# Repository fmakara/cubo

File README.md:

# cubo
C.U.B.O. - Montador de cubo mágico

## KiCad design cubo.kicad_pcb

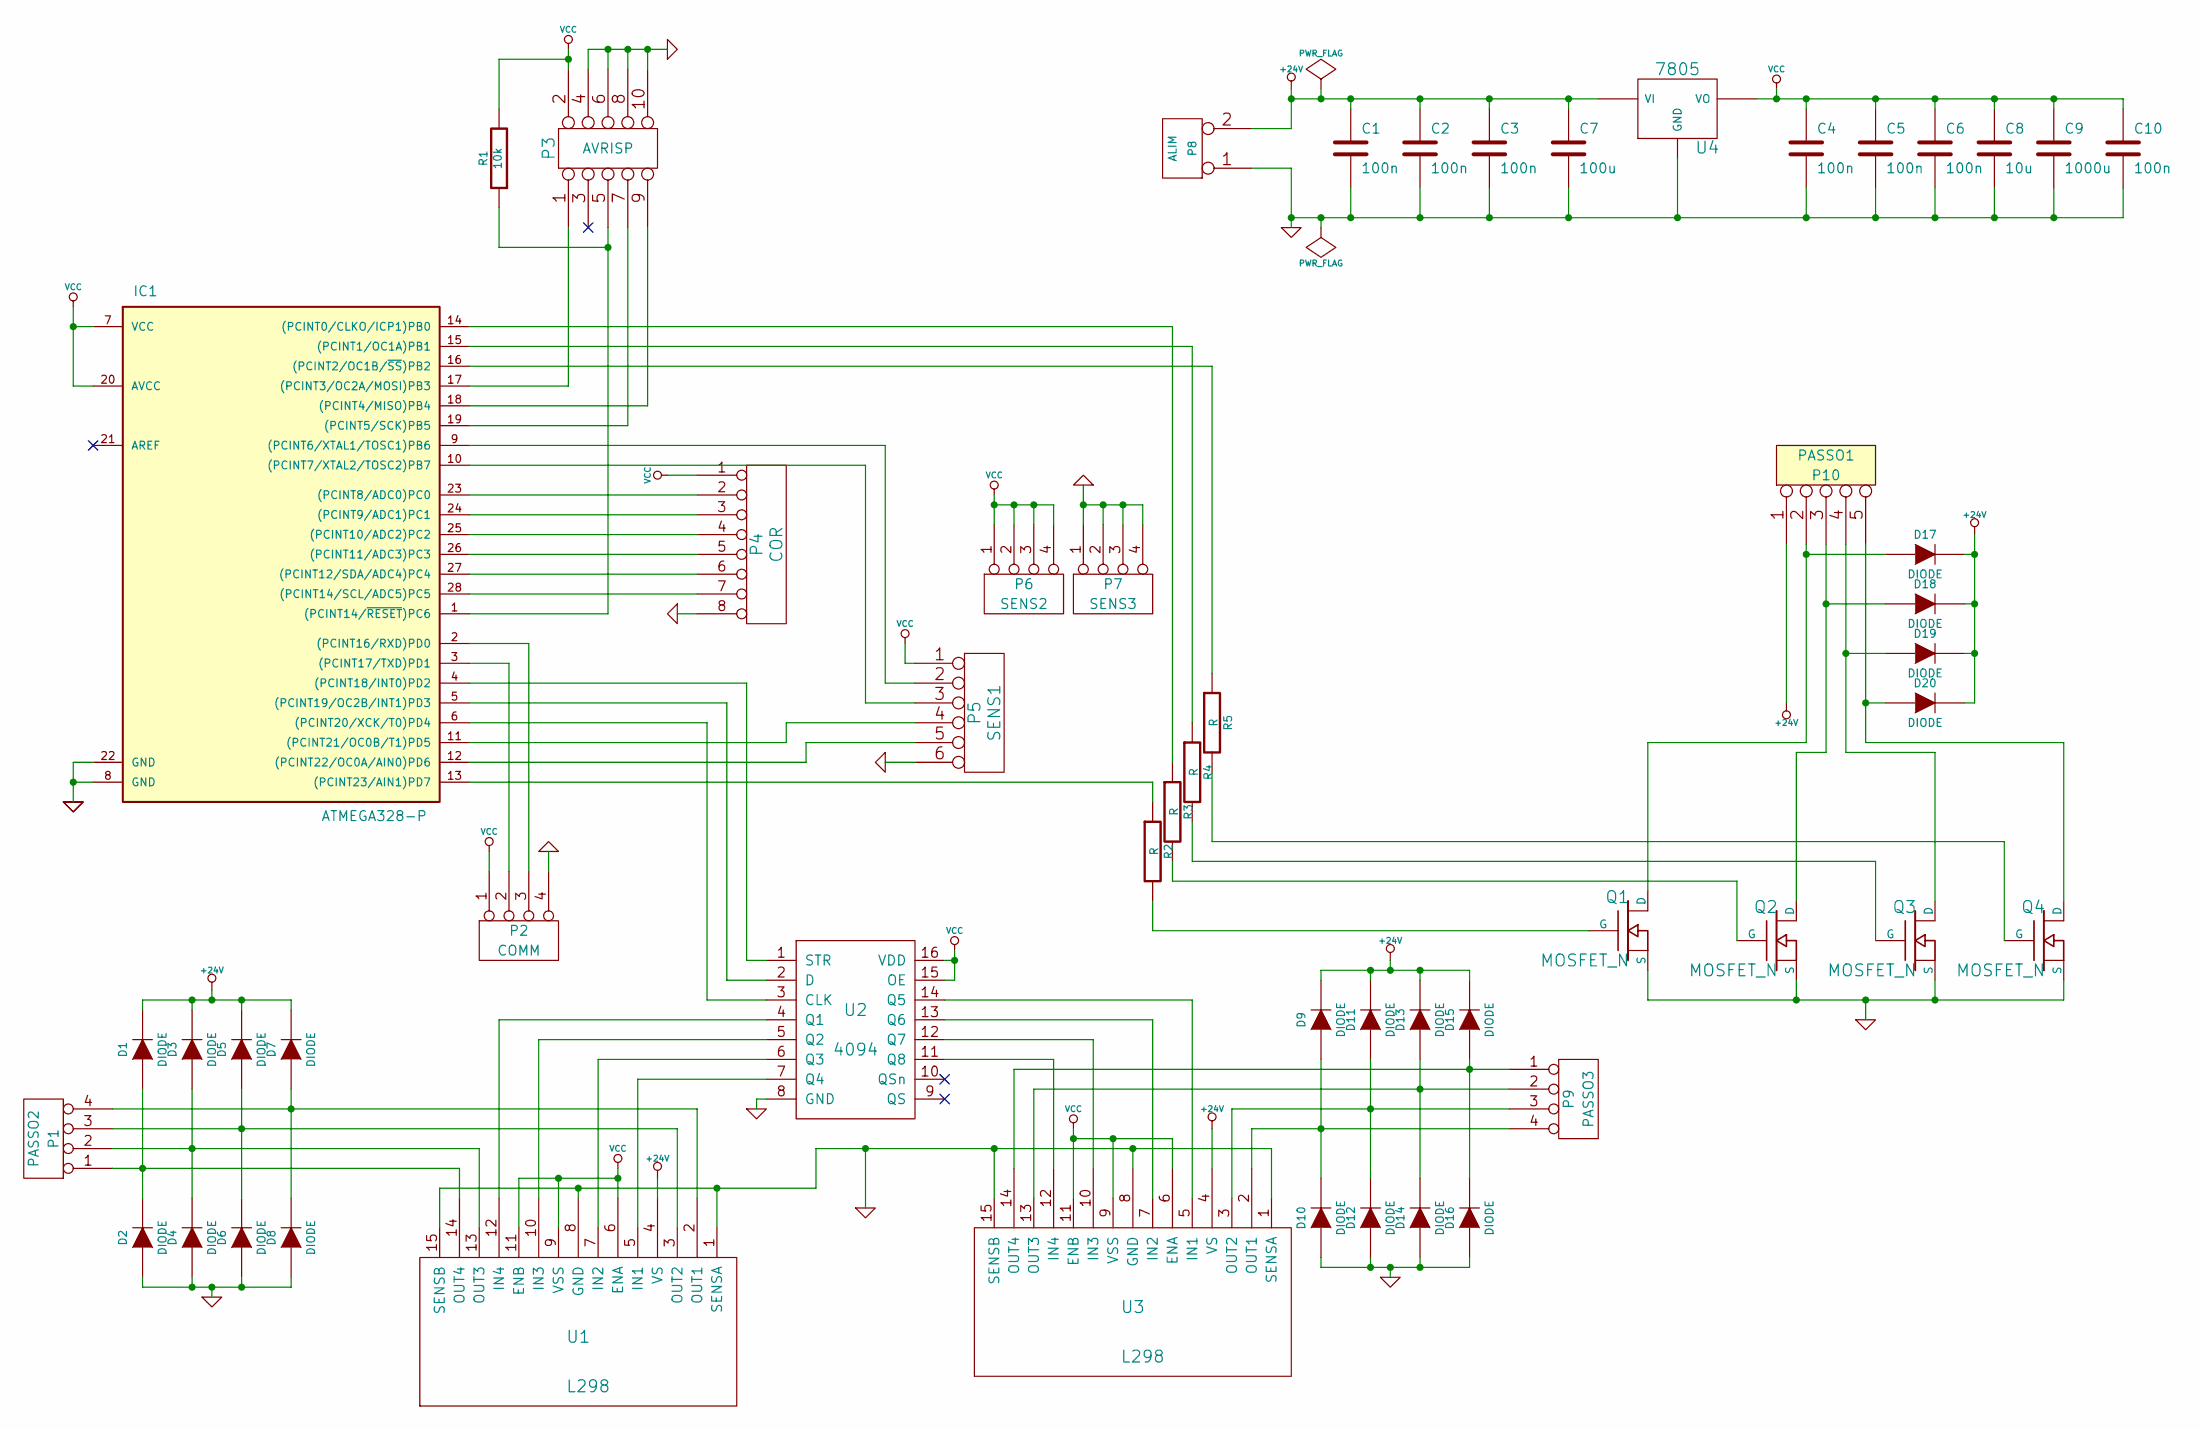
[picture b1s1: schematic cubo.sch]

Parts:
C1, C2, C3, C4, C5, C6, C10: 100n
C7: 100u
C8: 10u
C9: 1000u
D1, D2, D3, D4, D5, D6, D7, D8, D9, D10, D11, D12, D13, D14, D15, D16, D17, D18, D19, D20: DIODE
IC1: ATMEGA328-P; DIL28
P1: PASSO2
P2: COMM
P3: AVRISP
P4: COR
P5: SENS1
P6: SENS2
P7: SENS3
P8: ALIM
P9: PASSO3
P10: PASSO1
Q1, Q2, Q3, Q4: MOSFET_N
R1: 10k
R2, R3, R4, R5: R
U1, U3: L298
U2: 4094
U4: 7805

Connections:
+24V: C1.1, C2.1, C3.1, C7.1, D1.2 (K), D3.2 (K), D5.2 (K), D7.2 (K), D9.2 (K), D11.2 (K), D13.2 (K), D15.2 (K), D17.2 (K), D18.2 (K), D19.2 (K), D20.2 (K), P8.2 (PM), P10.1, U1.4 (VS), U3.4 (VS), U4.VI
GND: C1.2, C2.2, C3.2, C4.2, C5.2, C6.2, C7.2, C8.2, C9.2, C10.2, D2.1 (A), D4.1 (A), D6.1 (A), D8.1 (A), D10.1 (A), D12.1 (A), D14.1 (A), D16.1 (A), IC1.8 (GND), IC1.22 (GND), P2.4, P3.4, P3.6, P3.8, P3.10, P4.8, P5.6, P7.1, P7.2, P7.3, P7.4, P8.1, Q1.S, Q2.S, Q3.S, Q4.S, U1.1 (SENSA), U1.8 (GND), U1.15 (SENSB), U2.8 (GND), U3.1 (SENSA), U3.8 (GND), U3.15 (SENSB), U4.GND
unnamed: IC1.5 ((PCINT19/OC2B/INT1)PD3), U2.2 (D)
unnamed: IC1.2 ((PCINT16/RXD)PD0), P2.3
unnamed: IC1.9 ((PCINT6/XTAL1/TOSC1)PB6), P5.2
unnamed: IC1.19 ((PCINT5/SCK)PB5), P3.7
unnamed: IC1.18 ((PCINT4/MISO)PB4), P3.9
unnamed: IC1.3 ((PCINT17/TXD)PD1), P2.2
unnamed: Q3.G, R4.2
unnamed: IC1.15 ((PCINT1/OC1A)PB1), R4.1
unnamed: IC1.1 ((PCINT14/~RESET~)PC6), P3.5, R1.1
unnamed: IC1.16 ((PCINT2/OC1B/~SS~)PB2), R5.1
unnamed: IC1.13 ((PCINT23/AIN1)PD7), R2.1
unnamed: IC1.14 ((PCINT0/CLKO/ICP1)PB0), R3.1
unnamed: IC1.17 ((PCINT3/OC2A/MOSI)PB3), P3.1
unnamed: U2.12 (Q7), U3.10 (IN3)
unnamed: IC1.10 ((PCINT7/XTAL2/TOSC2)PB7), P5.3
unnamed: IC1.11 ((PCINT21/OC0B/T1)PD5), P5.4
unnamed: IC1.12 ((PCINT22/OC0A/AIN0)PD6), P5.5
unnamed: IC1.6 ((PCINT20/XCK/T0)PD4), U2.3 (CLK)
unnamed: U1.12 (IN4), U2.4 (Q1)
unnamed: U1.7 (IN2), U2.6 (Q3)
unnamed: IC1.27 ((PCINT12/SDA/ADC4)PC4), P4.6
unnamed: IC1.23 ((PCINT8/ADC0)PC0), P4.2
unnamed: IC1.24 ((PCINT9/ADC1)PC1), P4.3
unnamed: IC1.25 ((PCINT10/ADC2)PC2), P4.4
unnamed: IC1.26 ((PCINT11/ADC3)PC3), P4.5
unnamed: IC1.28 ((PCINT14/SCL/ADC5)PC5), P4.7
unnamed: Q4.G, R5.2
unnamed: D19.1 (A), P10.4, Q3.D
unnamed: D18.1 (A), P10.3, Q2.D
unnamed: Q2.G, R3.2
unnamed: Q1.G, R2.2
unnamed: D17.1 (A), P10.2, Q1.D
unnamed: D15.1 (A), D16.2 (K), P9.1, U3.14 (OUT4)
unnamed: D3.1 (A), D4.2 (K), P1.2, U1.13 (OUT3)
unnamed: D7.1 (A), D8.2 (K), P1.4, U1.2 (OUT1)
unnamed: D20.1 (A), P10.5, Q4.D
unnamed: IC1.4 ((PCINT18/INT0)PD2), U2.1 (STR)
unnamed: U2.13 (Q6), U3.7 (IN2)
unnamed: U1.10 (IN3), U2.5 (Q2)
unnamed: U1.5 (IN1), U2.7 (Q4)
unnamed: U2.11 (Q8), U3.12 (IN4)
unnamed: D11.1 (A), D12.2 (K), P9.3, U3.3 (OUT2)
unnamed: D9.1 (A), D10.2 (K), P9.4, U3.2 (OUT1)
unnamed: D1.1 (A), D2.2 (K), P1.1, U1.14 (OUT4)
unnamed: D5.1 (A), D6.2 (K), P1.3, U1.3 (OUT2)
unnamed: D13.1 (A), D14.2 (K), P9.2, U3.13 (OUT3)
unnamed: U2.14 (Q5), U3.5 (IN1)
VCC: C4.1, C5.1, C6.1, C8.1, C9.1, C10.1, IC1.7 (VCC), IC1.20 (AVCC), P2.1, P3.2, P4.1, P5.1, P6.1, P6.2, P6.3, P6.4, R1.2, U1.6 (ENA), U1.9 (VSS), U1.11 (ENB), U2.15 (OE), U2.16 (VDD), U3.6 (ENA), U3.9 (VSS), U3.11 (ENB), U4.VO

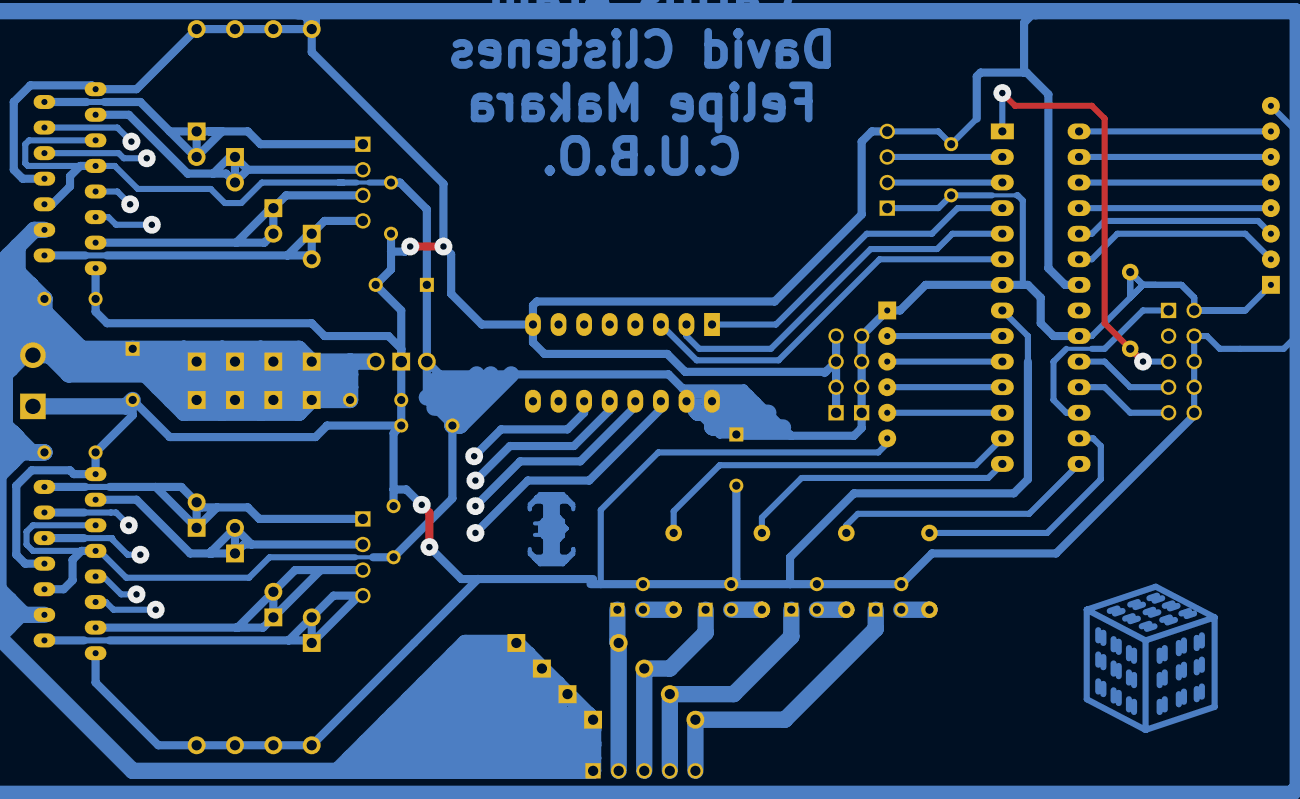
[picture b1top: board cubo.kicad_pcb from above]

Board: 2 copper layers, 54 parts (0 on the bottom side), 50 nets.

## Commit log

2016-06-08 Concluido
